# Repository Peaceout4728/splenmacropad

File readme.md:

My Splen Macropad is small keyboard that can be use for everyday uses. My Splen macropad has two columns, three rows, OLED display, and seven buttons. I use an app called Kicad to sketch and design my macropad. In kicad, I use the Schematic editor to create a layout of where I wanted my switches and diodes to go, then I went to pcb editor to arrange the switches and diodes to my liking. I went to Fusion to create 3D version of Macropad in its case.

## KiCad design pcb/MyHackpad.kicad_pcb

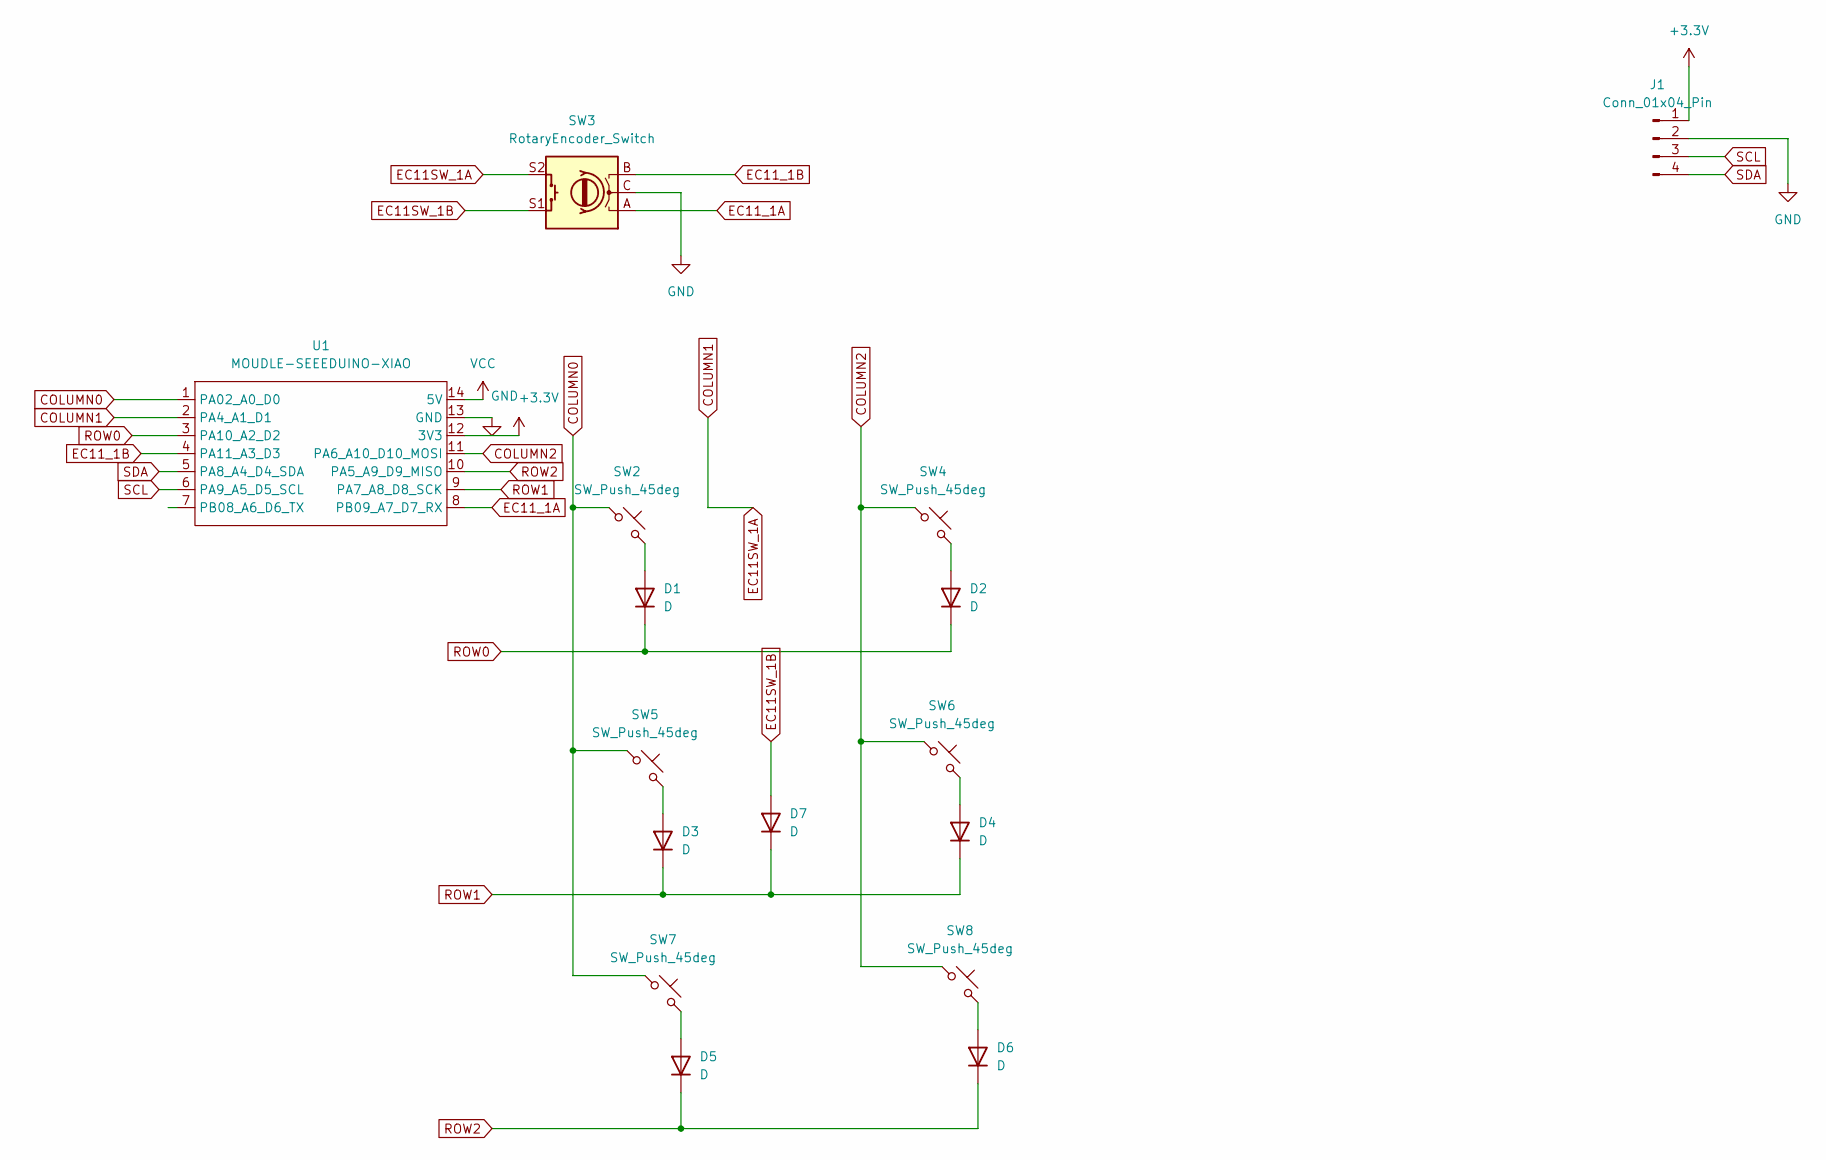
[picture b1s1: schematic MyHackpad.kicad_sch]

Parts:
D1, D2, D3, D4, D5, D6, D7: D; D_DO-35_SOD27_P7.62mm_Horizontal
J1: Conn_01x04_Pin; SSD1306-0.91-OLED-4pin-128x32
SW2, SW4, SW5, SW6, SW7, SW8: SW_Push_45deg; SW_Cherry_MX_1.00u_PCB
SW3: RotaryEncoder_Switch; RotaryEncoder_Alps_EC11E-Switch_Vertical_H20mm
U1: MOUDLE-SEEEDUINO-XIAO; XIAO-Generic-Hybrid-14P-2.54-21X17.8MM

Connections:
+3.3V: J1.1, U1.12 (3V3)
COLUMN0: SW2.1, SW5.1, SW7.1, U1.1 (PA02_A0_D0)
COLUMN1: SW3.S2, U1.2 (PA4_A1_D1)
COLUMN2: SW4.1, SW6.1, SW8.1, U1.11 (PA6_A10_D10_MOSI)
EC11SW_1B: D7.2 (A), SW3.S1
EC11_1A: SW3.A, U1.8 (PB09_A7_D7_RX)
EC11_1B: SW3.B, U1.4 (PA11_A3_D3)
GND: J1.2, SW3.C, U1.13 (GND)
unnamed: D1.2 (A), SW2.2
unnamed: D2.2 (A), SW4.2
unnamed: D3.2 (A), SW5.2
unnamed: D4.2 (A), SW6.2
unnamed: D5.2 (A), SW7.2
unnamed: D6.2 (A), SW8.2
ROW2: D5.1 (K), D6.1 (K), U1.10 (PA5_A9_D9_MISO)
SCL: J1.3, U1.6 (PA9_A5_D5_SCL)
SDA: J1.4, U1.5 (PA8_A4_D4_SDA)
VCC: U1.14 (5V)

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
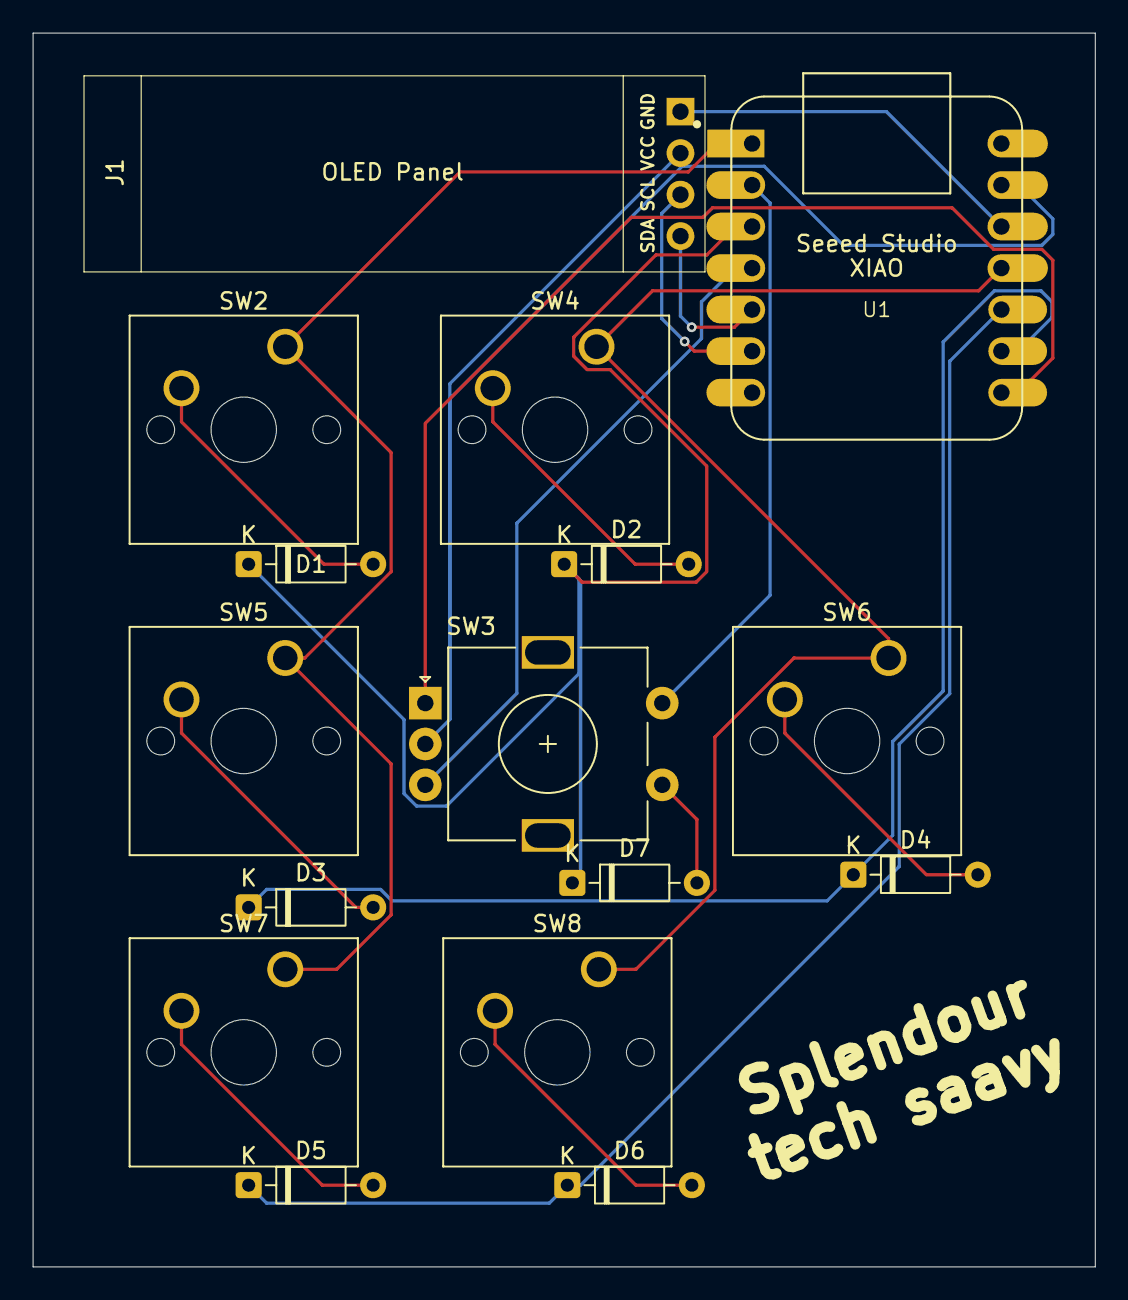
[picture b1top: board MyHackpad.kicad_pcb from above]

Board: 2 copper layers, 65.0 x 75.5 mm, 16 parts (0 on the bottom side), 19 nets.

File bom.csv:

Designator,Footprint,Quantity,Value,LCSC Part #
"D1, D2, D3, D4, D5, D6, D7",D_DO-35_SOD27_P7.62mm_Horizontal,7,D,
J1,SSD1306-0.91-OLED-4pin-128x32,1,Conn_01x04_Pin,
"SW2, SW4, SW5, SW6, SW7, SW8",SW_Cherry_MX_1.00u_PCB,6,SW_Push_45deg,
SW3,RotaryEncoder_Alps_EC11E-Switch_Vertical_H20mm,1,RotaryEncoder_Switch,
U1,XIAO-Generic-Hybrid-14P-2.54-21X17.8MM,1,MOUDLE-SEEEDUINO-XIAO,
